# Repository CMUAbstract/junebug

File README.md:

# Junebug

Junebug is an embedded platform for low-power computing in extreme environments.
It is designed to support intermittent computing and machine learning in outer
space. Junebug is a chipsat or gram-scale satellite development platform.

## Directory Contents

* [components](components/README.md): KiCad component library files
* [datasheets](datasheets/README.md): Component datasheets
* [footprints](footprints/README.md): KiCad component footprint files
* [kicad](kicad/README.md): KiCad project files
* [BOM.csv](bom.csv): Bill of materials
* [NOTES.md](notes.md): Project notes
* [README.md](README.md): This document

## License

Copyright 2019 Bradley Denby

Licensed under the Apache License, Version 2.0 (the "License"); you may not use
this file except in compliance with the License. You may obtain a copy of the
License at <http://www.apache.org/licenses/LICENSE-2.0>.

Unless required by applicable law or agreed to in writing, software distributed
under the License is distributed on an "AS IS" BASIS, WITHOUT WARRANTIES OR
CONDITIONS OF ANY KIND, either express or implied. See the License for the
specific language governing permissions and limitations under the License.

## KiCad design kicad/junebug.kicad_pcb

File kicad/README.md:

# KiCad

KiCad project files.

## License

Copyright 2019 Bradley Denby

Licensed under the Apache License, Version 2.0 (the "License"); you may not use
this file except in compliance with the License. You may obtain a copy of the
License at <http://www.apache.org/licenses/LICENSE-2.0>.

Unless required by applicable law or agreed to in writing, software distributed
under the License is distributed on an "AS IS" BASIS, WITHOUT WARRANTIES OR
CONDITIONS OF ANY KIND, either express or implied. See the License for the
specific language governing permissions and limitations under the License.

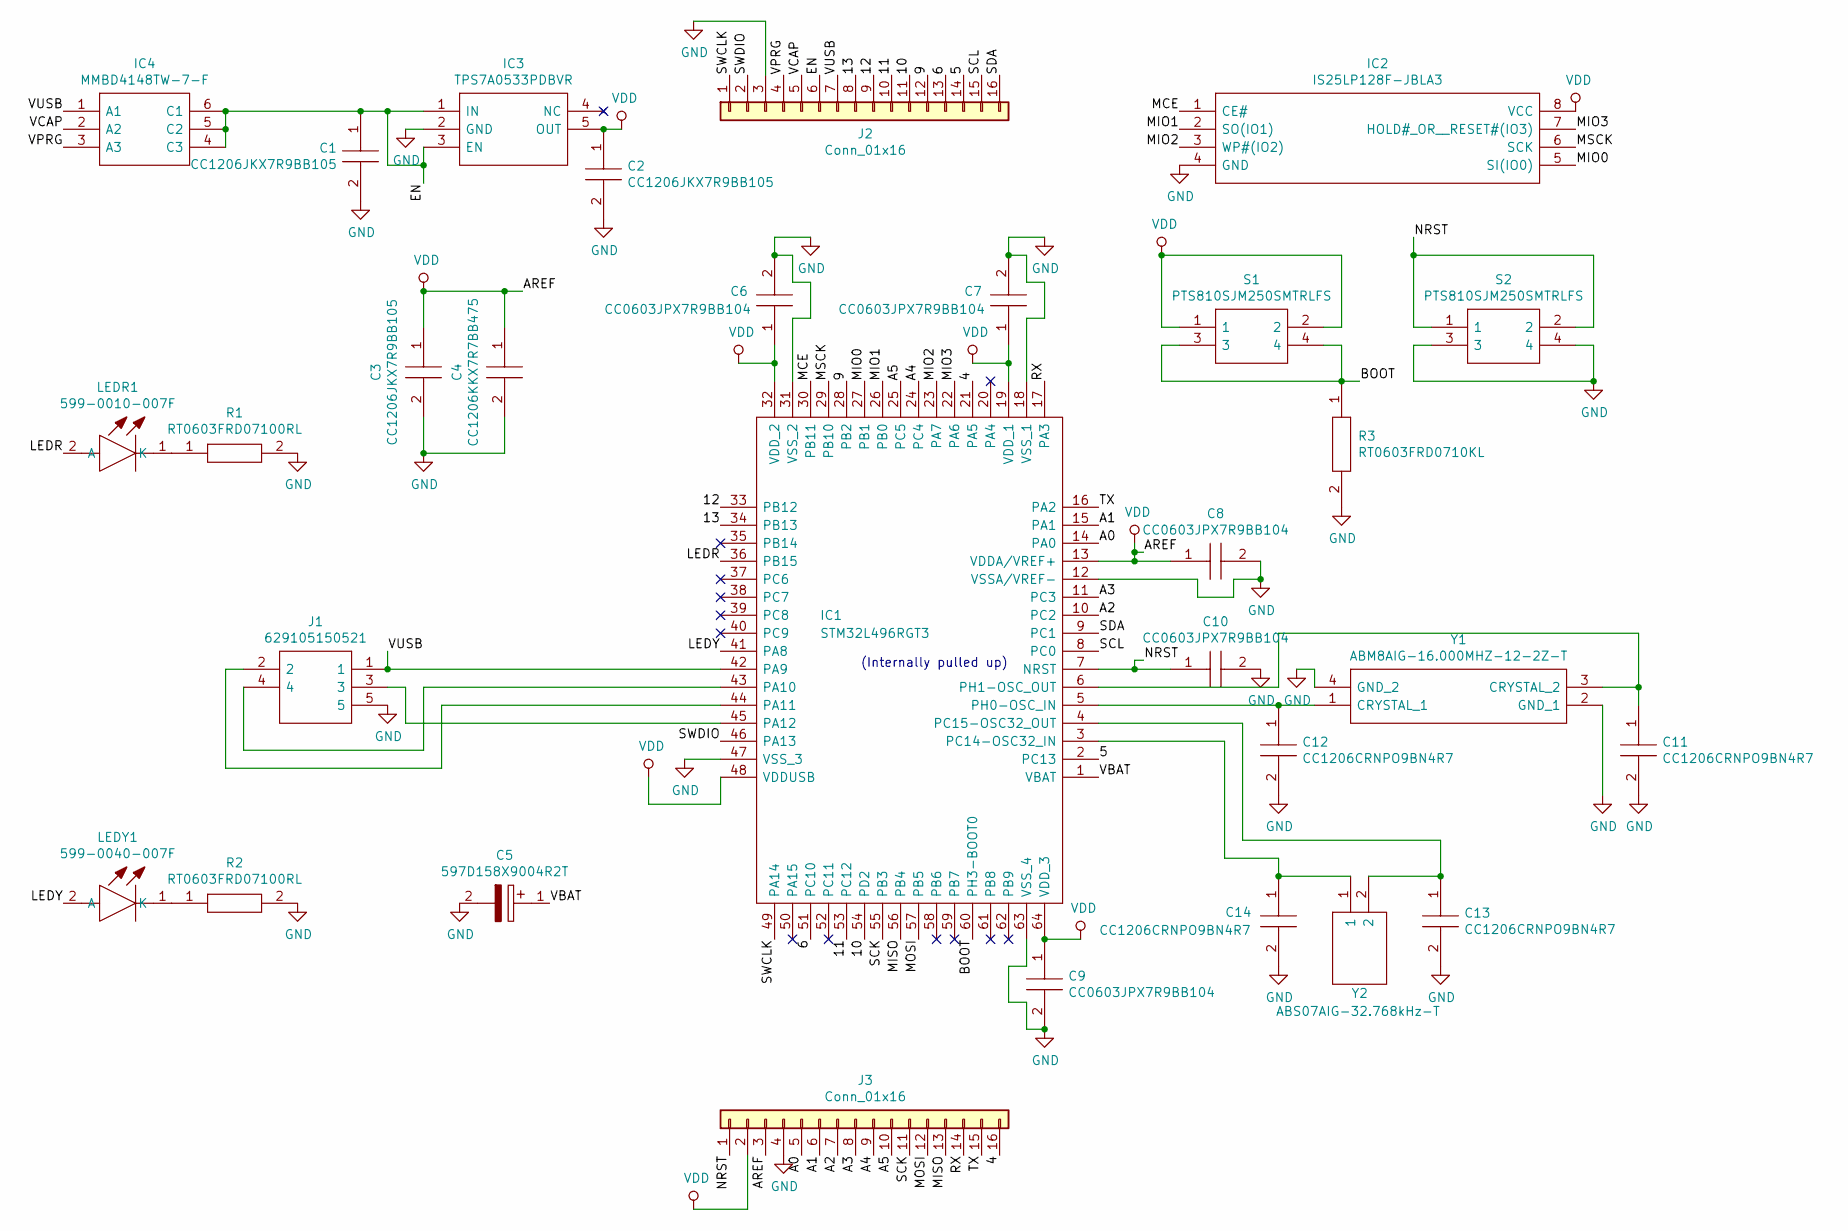
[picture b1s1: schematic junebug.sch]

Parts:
C1, C2, C3: CC1206JKX7R9BB105; CAPC3216X180N; Manufacturer_Part_Number CC1206JKX7R9BB105; Mouser Part Number 603-CC1206JK7R9BB105
C4: CC1206KKX7R7BB475; CAPC3216X180N; Manufacturer_Part_Number CC1206KKX7R7BB475; Mouser Part Number 603-CC126KKX7R7BB475
C5: 597D158X9004R2T; Manufacturer_Part_Number 597D158X9004R2T; Mouser Part Number 71-597D158X9004R2T
C6, C7, C8, C9, C10: CC0603JPX7R9BB104; CAPC1608X90N; Manufacturer_Part_Number CC0603JPX7R9BB104; Mouser Part Number 603-CC0603JPX79BB104
C11, C12, C13, C14: CC1206CRNPO9BN4R7; CAPC3216X70N; Manufacturer_Part_Number CC1206CRNPO9BN4R7; Mouser Part Number 603-C1206CRNPO9BN4R7
IC1: STM32L496RGT3; QFP50P1200X1200X160-64N; Manufacturer_Part_Number STM32L496RGT3; Mouser Part Number 511-STM32L496RGT3
IC2: IS25LP128F-JBLA3; SOIC127P790X216-8N; Manufacturer_Part_Number IS25LP128F-JBLA3; Mouser Part Number 870-IS25LP128F-JBLA3
IC3: TPS7A0533PDBVR; SOT95P280X145-5N; Manufacturer_Part_Number TPS7A0533PDBVR; Mouser Part Number 595-TPS7A0533PDBVR
IC4: MMBD4148TW-7-F; SOT65P210X110-6N; Manufacturer_Part_Number MMBD4148TW-7-F; Mouser Part Number 621-MMBD4148TW-7-F
J1: 629105150521; USB_Micro-B_Wuerth_629105150521; Manufacturer_Part_Number 629105150521; Mouser Part Number 710-629105150521
J2, J3: Conn_01x16; PinSocket_1x16_Feather
LEDR1: 599-0010-007F; LEDM168X70N; Manufacturer_Part_Number 599-0010-007F; Mouser Part Number 645-599-0010-007F
LEDY1: 599-0040-007F; LEDM168X70N; Manufacturer_Part_Number 599-0040-007F; Mouser Part Number 645-599-0040-007F
R1, R2: RT0603FRD07100RL; RESC1608X55N; Manufacturer_Part_Number RT0603FRD07100RL; Mouser Part Number 603-RT0603FRD07100RL
R3: RT0603FRD0710KL; RESC1608X55N; Manufacturer_Part_Number RT0603FRD0710KL; Mouser Part Number 603-RT0603FRD0710KL
S1, S2: PTS810SJM250SMTRLFS; PTS810SJG250SMTRLFS; Manufacturer_Part_Number PTS810SJM250SMTRLFS; Mouser Part Number 611-PTS810SJM250SMTR
Y1: ABM8AIG-16.000MHZ-12-2Z-T; ABM8AIG25000MHZ122ZT3; Manufacturer_Part_Number ABM8AIG-16.000MHZ-12-2Z-T; Mouser Part Number 815-ABM8AIG16122ZT
Y2: ABS07AIG-32.768kHz-T; ABS07AIG32768kHz71T; Manufacturer_Part_Number ABS07AIG-32.768kHz-T; Mouser Part Number 815-S07AIG-32.768T

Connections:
/4: IC1.21 (PA5), J3.16
/5: IC1.2 (PC13), J2.14
/6: IC1.51 (PC10), J2.13
/9: IC1.28 (PB2), J2.12
/10: IC1.54 (PD2), J2.11
/11: IC1.53 (PC12), J2.10
/12: IC1.33 (PB12), J2.9
/13: IC1.34 (PB13), J2.8
/A0: IC1.14 (PA0), J3.5
/A1: IC1.15 (PA1), J3.6
/A2: IC1.10 (PC2), J3.7
/A3: IC1.11 (PC3), J3.8
/A4: IC1.24 (PC4), J3.9
/A5: IC1.25 (PC5), J3.10
/BOOT: IC1.60 (PH3-BOOT0), R3.1, S1.3, S1.4
/EN: C1.1, IC3.1 (IN), IC3.3 (EN), IC4.4 (C3), IC4.5 (C2), IC4.6 (C1), J2.6
/LEDR: IC1.36 (PB15), LEDR1.2 (A)
/LEDY: IC1.41 (PA8), LEDY1.2 (A)
/MCE: IC1.30 (PB11), IC2.1 (CE#)
/MIO0: IC1.27 (PB1), IC2.5 (SI(IO0))
/MIO1: IC1.26 (PB0), IC2.2 (SO(IO1))
/MIO2: IC1.23 (PA7), IC2.3 (WP#(IO2))
/MIO3: IC1.22 (PA6), IC2.7 (HOLD#_OR__RESET#(IO3))
/MISO: IC1.56 (PB4), J3.13
/MOSI: IC1.57 (PB5), J3.12
/MSCK: IC1.29 (PB10), IC2.6 (SCK)
/NRST: C10.1, IC1.7 (NRST), J3.1, S2.1, S2.2
/RX: IC1.17 (PA3), J3.14
/SCK: IC1.55 (PB3), J3.11
/SCL: IC1.8 (PC0), J2.15
/SDA: IC1.9 (PC1), J2.16
/SWCLK: IC1.49 (PA14), J2.1
/SWDIO: IC1.46 (PA13), J2.2
/TX: IC1.16 (PA2), J3.15
/VBAT: C5.1, IC1.1 (VBAT)
/VCAP: IC4.2 (A2), J2.5
/VPRG: IC4.3 (A3), J2.4
/VUSB: IC1.42 (PA9), IC4.1 (A1), J1.1, J2.7
GND: C1.2, C2.2, C3.2, C4.2, C5.2, C6.2, C7.2, C8.2, C9.2, C10.2, C11.2, C12.2, C13.2, C14.2, IC1.12 (VSSA/VREF-), IC1.18 (VSS_1), IC1.31 (VSS_2), IC1.47 (VSS_3), IC1.63 (VSS_4), IC2.4 (GND), IC3.2 (GND), J1.5, J2.3, J3.4, R1.2, R2.2, R3.2, S2.3, S2.4, Y1.2 (GND_1), Y1.4 (GND_2)
unnamed: C11.1, IC1.6 (PH1-OSC_OUT), Y1.3 (CRYSTAL_2)
unnamed: C12.1, IC1.5 (PH0-OSC_IN), Y1.1 (CRYSTAL_1)
unnamed: C13.1, IC1.4 (PC15-OSC32_OUT), Y2.2
unnamed: C14.1, IC1.3 (PC14-OSC32_IN), Y2.1
unnamed: IC1.43 (PA10), J1.4
unnamed: IC1.44 (PA11), J1.2
unnamed: IC1.45 (PA12), J1.3
unnamed: LEDR1.1 (K), R1.1
unnamed: LEDY1.1 (K), R2.1
VDD: C2.1, C3.1, C4.1, C6.1, C7.1, C8.1, C9.1, IC1.13 (VDDA/VREF+), IC1.19 (VDD_1), IC1.32 (VDD_2), IC1.48 (VDDUSB), IC1.64 (VDD_3), IC2.8 (VCC), IC3.5 (OUT), J3.2, J3.3, S1.1, S1.2

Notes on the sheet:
(Internally pulled up)

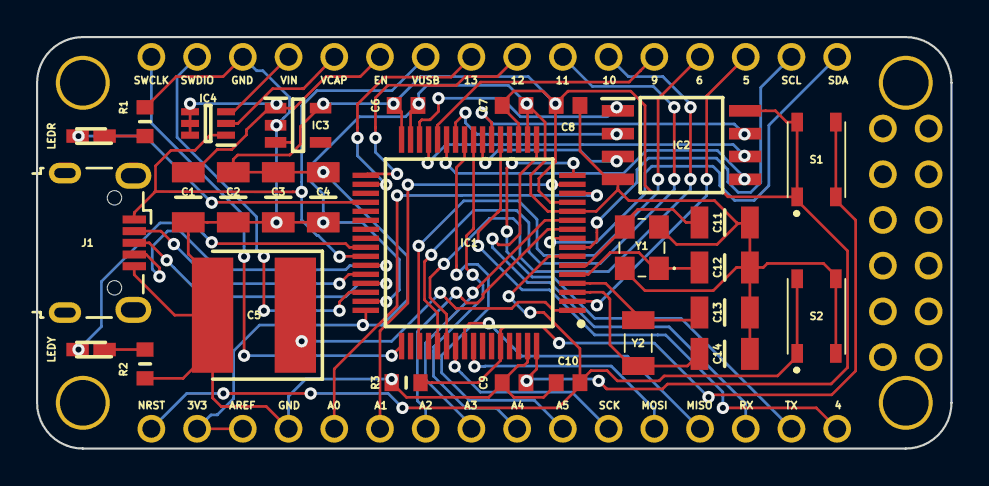
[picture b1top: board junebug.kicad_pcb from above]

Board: 2 copper layers, 50.8 x 22.9 mm, 31 parts (1 on the bottom side), 49 nets.

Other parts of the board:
cmu-logo: cmu-logo

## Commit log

2019-12-30 Base design
